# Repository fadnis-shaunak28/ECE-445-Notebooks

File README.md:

# ECE-445-Notebooks
Lab Notebooks for ECE 445

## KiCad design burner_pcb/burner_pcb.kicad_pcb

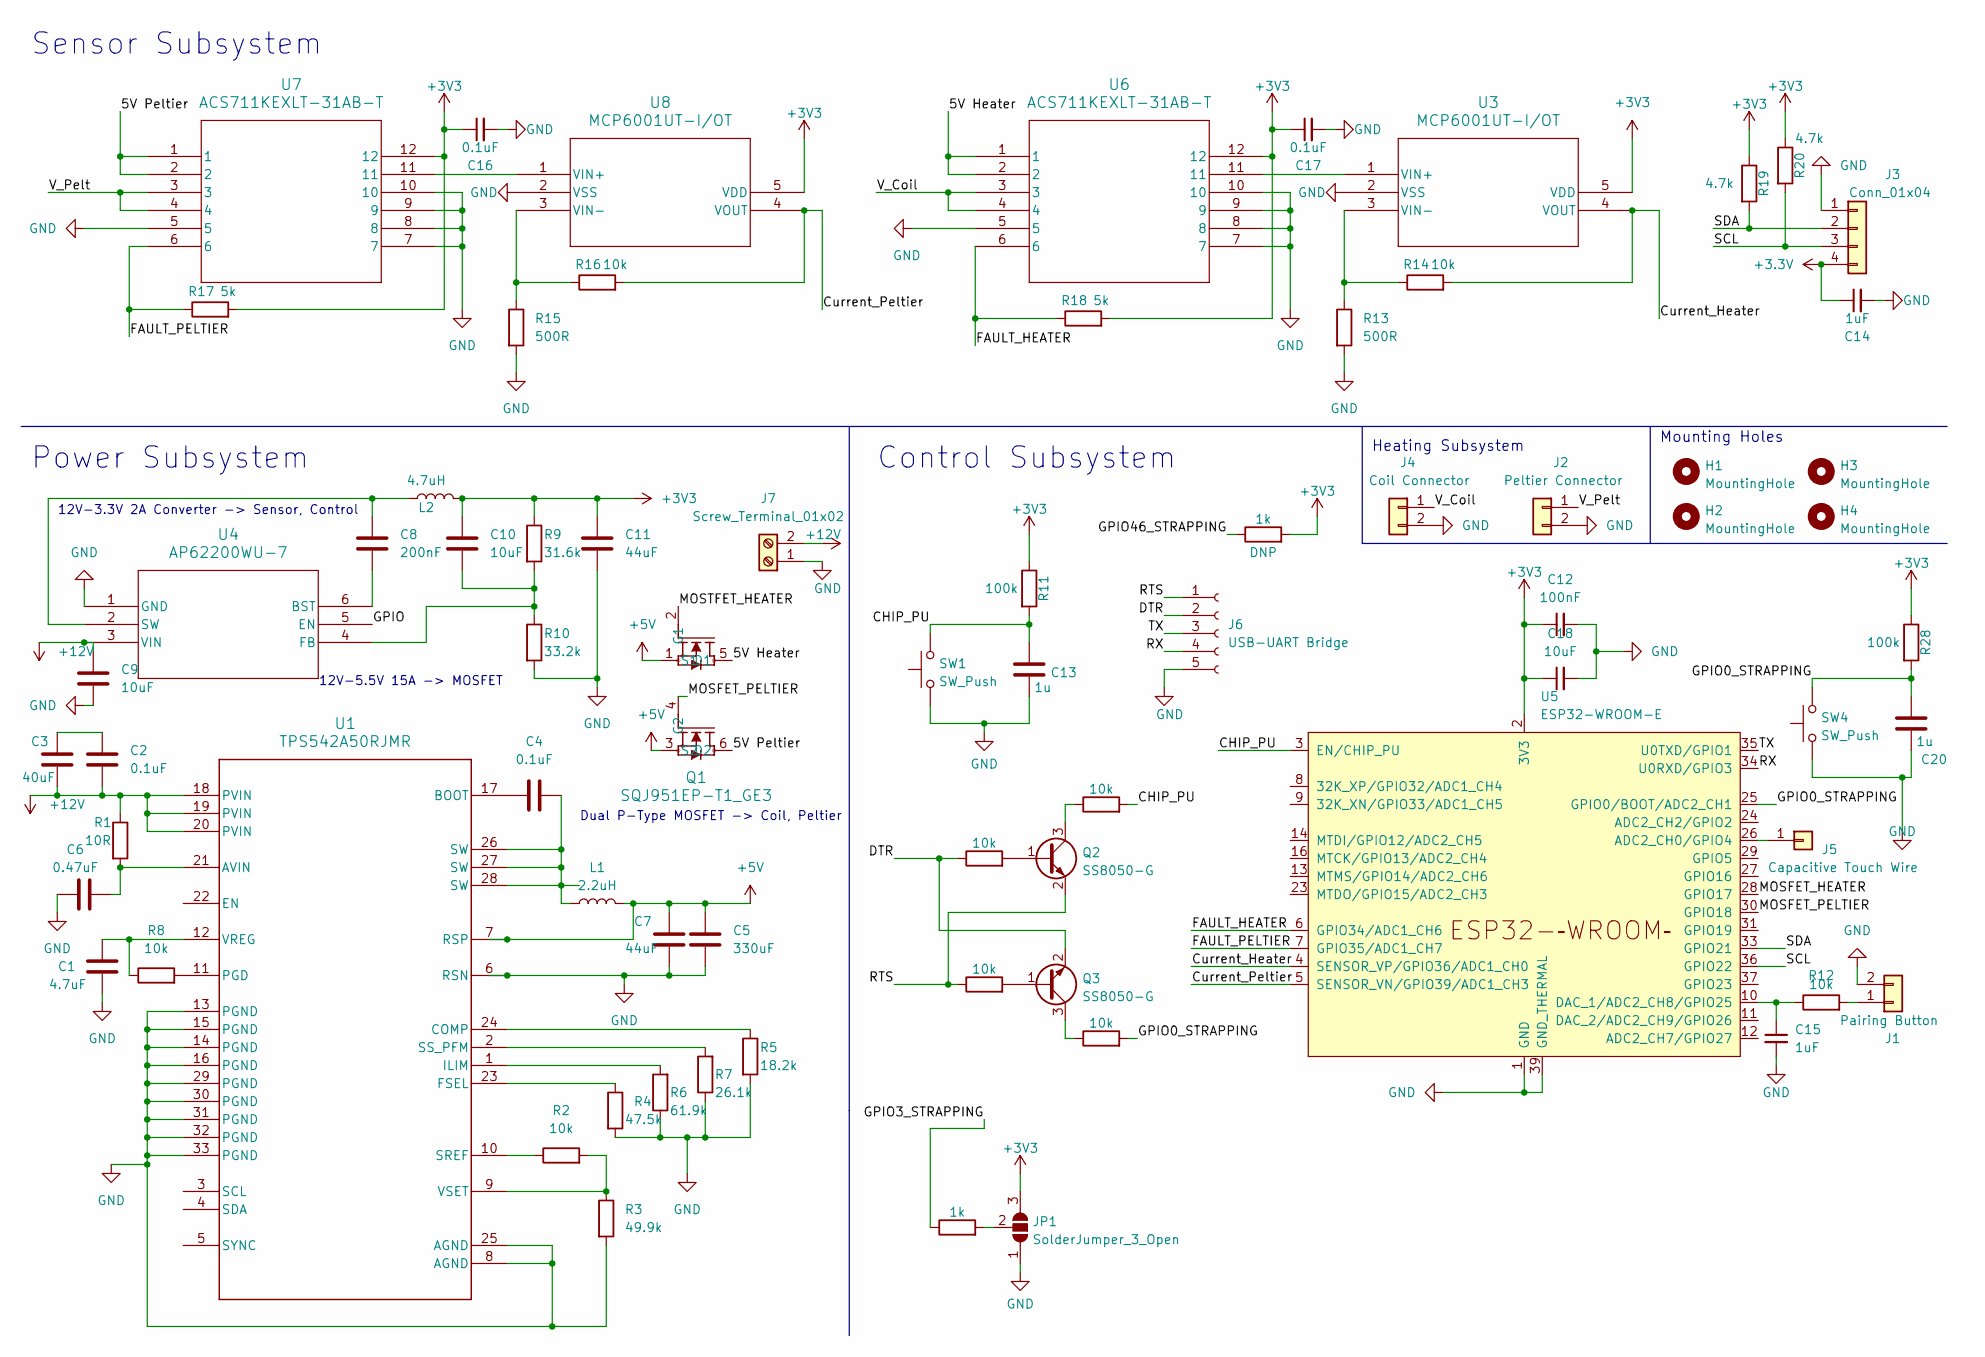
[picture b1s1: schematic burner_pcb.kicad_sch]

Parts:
C1: 4.7uF; C_0805_2012Metric
C2, C4, C16, C17: 0.1uF; C_0805_2012Metric
C3: 40uF; C_0805_2012Metric
C5: 330uF; C_0805_2012Metric
C6: 0.47uF; C_0805_2012Metric
C7, C11: 44uF; C_0805_2012Metric
C8: 200nF; C_0805_2012Metric
C9, C10, C18: 10uF; C_0805_2012Metric
C12: 100nF; C_0805_2012Metric
C13, C20: 1u; C_0805_2012Metric
C14, C15: 1uF; C_0805_2012Metric
H1, H2, H3, H4: MountingHole; MountingHole_3.2mm_M3
J1: Pairing Button; Molex_KK-254_AE-6410-02A_1x02_P2.54mm_Vertical
J2: Peltier Connector; Molex_KK-254_AE-6410-02A_1x02_P2.54mm_Vertical
J3: Conn_01x04; Molex_KK-254_AE-6410-04A_1x04_P2.54mm_Vertical
J4: Coil Connector; TerminalBlock_TE_282834-2_1x02_P2.54mm_Horizontal
J5: Capacitive Touch Wire; PinHeader_1x01_P1.00mm_Vertical
J6: USB-UART Bridge; PinHeader_1x05_P2.54mm_Vertical
J7: Screw_Terminal_01x02; TerminalBlock_TE_282834-2_1x02_P2.54mm_Horizontal
JP1: SolderJumper_3_Open; SolderJumper-3_P2.0mm_Open_TrianglePad1.0x1.5mm
L1: 2.2uH; L_0805_2012Metric
L2: 4.7uH; L_0805_2012Metric
Q1: SQJ951EP-T1_GE3; MOSFET_DEP-T1_GE3_VIS
Q2, Q3: SS8050-G; SOT-23
R1: 10R; R_0805_2012Metric
R2, R8, R12, R14, R16, R22, R23, R25, R26: 10k; R_0805_2012Metric
R3: 49.9k; R_0805_2012Metric
R4: 47.5k; R_0805_2012Metric
R5: 18.2k; R_0805_2012Metric
R6: 61.9k; R_0805_2012Metric
R7: 26.1k; R_0805_2012Metric
R9: 31.6k; R_0805_2012Metric
R10: 33.2k; R_0805_2012Metric
R11, R28: 100k; R_0805_2012Metric
R13, R15: 500R; R_0805_2012Metric
R17, R18: 5k; R_0805_2012Metric
R19, R20: 4.7k; R_0805_2012Metric
R21, R24: 1k; R_0805_2012Metric
SW1, SW4: SW_Push; SW_SPST_B3S-1000
U1: TPS542A50RJMR; RJM0033A
U3, U8: MCP6001UT-I/OT; SOT-23-5_MC_MCH
U4: AP62200WU-7; TSOT26-WU_DIO
U5: ESP32-WROOM-E; ESP32-WROOM-32E
U6, U7: ACS711KEXLT-31AB-T; QFN12_ACS711KEXLT-31AB-T_ALM

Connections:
+3.3V: C14.1, J3.4
+3V3: C10.2, C11.2, C12.1, C16.1, C17.1, C18.1, JP1.3 (B), L2.2, R9.1, R11.1, R17.2, R18.2, R19.1, R20.1, R21.2, R28.1, U3.5 (VDD), U5.2 (3V3), U6.12, U7.12, U8.5 (VDD)
+5V: C5.1, C7.1, L1.2, Q1.1 (S1), Q1.3 (S2), U1.7 (RSP)
+12V: C2.2, C3.2, C9.2, J7.2, R1.1, U1.18 (PVIN), U1.19 (PVIN), U1.20 (PVIN), U4.3 (VIN)
/5V Heater: Q1.5 (D1), U6.1, U6.2
/5V Peltier: Q1.6 (D2), U7.1, U7.2
/CHIP_PU: C13.1, R11.2, R25.2, SW1.2, U5.3 (EN/CHIP_PU)
/Current_Heater: R14.2, U3.4 (VOUT), U5.4 (SENSOR_VP/GPIO36/ADC1_CH0)
/Current_Peltier: R16.2, U5.5 (SENSOR_VN/GPIO39/ADC1_CH3), U8.4 (VOUT)
/DTR: J6.2, Q3.2 (E), R22.1
/FAULT_HEATER: R18.1, U5.6 (GPIO34/ADC1_CH6), U6.6
/FAULT_PELTIER: R17.1, U5.7 (GPIO35/ADC1_CH7), U7.6
/GPIO: U4.5 (EN)
/GPIO0_STRAPPING: C20.1, R26.2, R28.2, SW4.2, U5.25 (GPIO0/BOOT/ADC2_CH1)
/GPIO3_STRAPPING: R24.1
/GPIO46_STRAPPING: R21.1
/MOSFET_HEATER: U5.28 (GPIO17)
/MOSFET_PELTIER: Q1.4 (G2), U5.30 (GPIO18)
/MOSTFET_HEATER: Q1.2 (G1)
/RTS: J6.1, Q2.2 (E), R23.1
/RX: J6.4, U5.34 (U0RXD/GPIO3)
/SCL: J3.3, R20.2, U5.36 (GPIO22)
/SDA: J3.2, R19.2, U5.33 (GPIO21)
/TX: J6.3, U5.35 (U0TXD/GPIO1)
/V_Coil: J4.1, U6.3, U6.4
/V_Pelt: J2.1, U7.3, U7.4
GND: C1.2, C5.2, C6.1, C7.2, C9.1, C11.1, C12.2, C13.2, C14.2, C15.2, C16.2, C17.2, C18.2, C20.2, J1.2, J2.2, J3.1, J4.2, J6.5, J7.1, JP1.1 (A), R3.2, R4.2, R5.2, R6.1, R7.1, R10.2, R13.2, R15.2, SW1.1, SW4.1, U1.6 (RSN), U1.8 (AGND), U1.13 (PGND), U1.14 (PGND), U1.15 (PGND), U1.16 (PGND), U1.25 (AGND), U1.29 (PGND), U1.30 (PGND), U1.31 (PGND), U1.32 (PGND), U1.33 (PGND), U3.2 (VSS), U4.1 (GND), U5.1 (GND), U5.15 (GND), U5.38 (GND), U5.39 (GND_THERMAL), U6.5, U6.7, U6.8, U6.9, U6.10, U7.5, U7.7, U7.8, U7.9, U7.10, U8.2 (VSS)
unnamed: C2.1, C3.1
unnamed: C4.2, L1.1, U1.26 (SW), U1.27 (SW), U1.28 (SW)
unnamed: J1.1, R12.2
unnamed: J5.1, U5.26 (ADC2_CH0/GPIO4)
unnamed: JP1.2 (C), R24.2
unnamed: Q2.1 (B), R22.2
unnamed: Q2.3 (C), R25.1
unnamed: Q3.1 (B), R23.2
unnamed: Q3.3 (C), R26.1
unnamed: C6.2, R1.2, U1.21 (AVIN)
unnamed: C4.1, U1.17 (BOOT)
unnamed: R5.1, U1.24 (COMP)
unnamed: R4.1, U1.23 (FSEL)
unnamed: R6.2, U1.1 (ILIM)
unnamed: R8.2, U1.11 (PGD)
unnamed: R2.1, U1.10 (SREF)
unnamed: R7.2, U1.2 (SS_PFM)
unnamed: C1.1, R8.1, U1.12 (VREG)
unnamed: R2.2, R3.1, U1.9 (VSET)
unnamed: U3.1 (VIN+), U6.11
unnamed: R13.1, R14.1, U3.3 (VIN-)
unnamed: C8.1, U4.6 (BST)
unnamed: C10.1, R9.2, R10.1, U4.4 (FB)
unnamed: C8.2, L2.1, U4.2 (SW)
unnamed: C15.1, R12.1, U5.10 (DAC_1/ADC2_CH8/GPIO25)
unnamed: U7.11, U8.1 (VIN+)
unnamed: R15.1, R16.1, U8.3 (VIN-)

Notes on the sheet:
Heating Subsystem
Dual P-Type MOSFET -> Coil, Peltier
Control Subsystem
Power Subsystem
Mounting Holes
12V-5.5V 15A -> MOSFET
12V-3.3V 2A Converter -> Sensor, Control
Sensor Subsystem

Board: 2 copper layers, 72 parts (0 on the bottom side), 49 nets, no tracks yet.

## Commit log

2024-02-06 Making block diagram for proposal/TA meeting
2024-02-06 Added Proposal Diagram
2024-02-06 added block diagram draft
2024-02-08 updated block diagram
2024-02-17 updated block diagram to include current sensors, and power subsystem changs
2024-02-22 added power subsystem schematic
2024-02-22 added full schematic
2024-02-22 block diagram finished
2024-02-22 finished block diagram
2024-02-23 added subsystem kicad screenshots
2024-03-06 finished schematic and loaded footprints in
2024-03-26 Added gerber zip file for first board
2024-05-02 finishing notebook
2024-05-02 finished lab notebook
2024-05-02 Rename Screen Shot 2024-05-02 at 2.07.16 PM.png to tolanalysis
2024-05-03 Rename Screen Shot 2024-03-27 at 7.05.23 PM.png to swiftui.png
2024-05-03 Rename Screen Shot 2024-05-01 at 4.50.19 PM.png to MITapp.png
2024-05-03 Done with Notebook
